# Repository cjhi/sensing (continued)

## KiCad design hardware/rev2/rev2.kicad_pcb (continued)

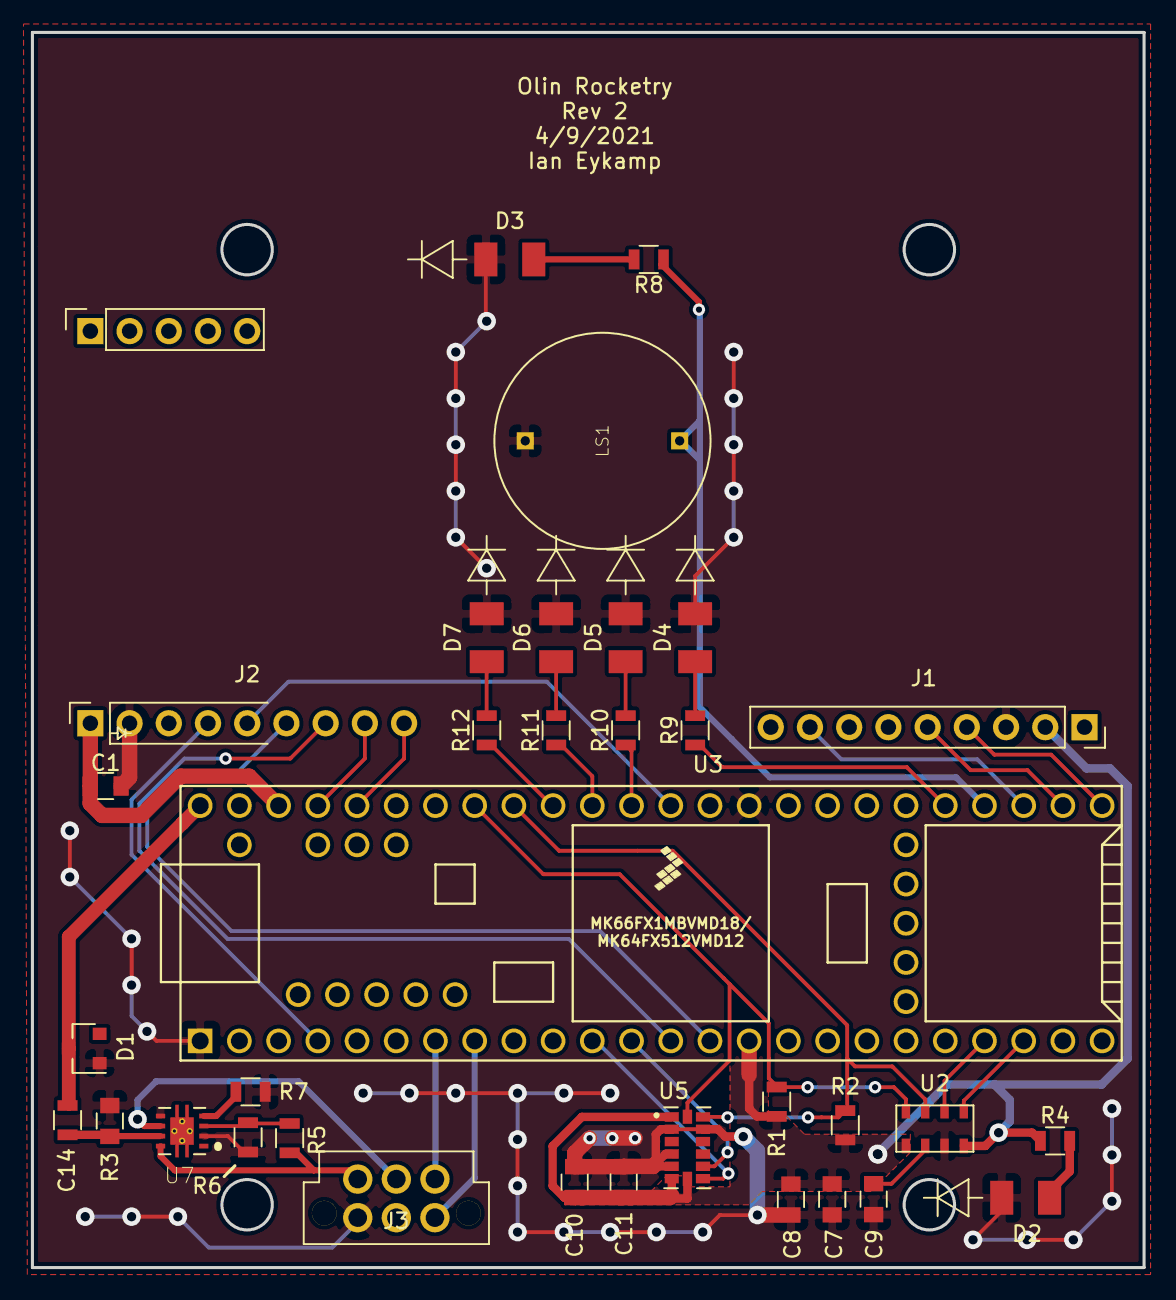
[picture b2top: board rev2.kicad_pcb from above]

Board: 2 copper layers, 72.0 x 80.0 mm, 34 parts (1 on the bottom side), 38 nets.

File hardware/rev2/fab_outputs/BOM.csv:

"Comment","Designator","Footprint","LCSC Part #","LCSC Part Type"

"Conn_02x03_Odd_Even","J3","Molex_Nano-Fit_105312-1106","",""

"LED","D2,D3,D4,D5,D6,D7","AA3528LSECKT-J4","",""

"PKB24SPCH3601-B0","LS1","PT-1340","",""

"100n","C7,C9,C10","C_0805_OEM","",""

"10u","C8","C_0805_OEM","",""

"R_4.99K","R1,R2","R_0805_OEM","",""

"MPL3115A2","U2","MPL3115A2","",""

"Teensy3.6","U3","Teensy3-6","",""

"1u","C11","C_0805_OEM","",""

"ADXL345BCCZ","U5","ADXL345","",""

"RFM9X_header","J2","RFM9X_header","",""

"Conn_01x09_Female","J1","PinSocket_1x09_P2.54mm_Vertical","",""

"R_20k","R5","R_0805_OEM","",""

"C_1uF","C14","C_0805_OEM","",""

"R_8k","R6","R_0805_OEM","",""

"R_475","R7","R_0805_OEM","",""

"TPS2113ADRBR","U7","TPS2113ADRBR","",""

"C_10uF","C1","C_0805_OEM","",""

"D_Zener","D1","SOT-23","",""

"R_20","R3","R_0805_OEM","",""

"R_750","R4,R8,R9,R10,R11,R12","R_0805_OEM","",""

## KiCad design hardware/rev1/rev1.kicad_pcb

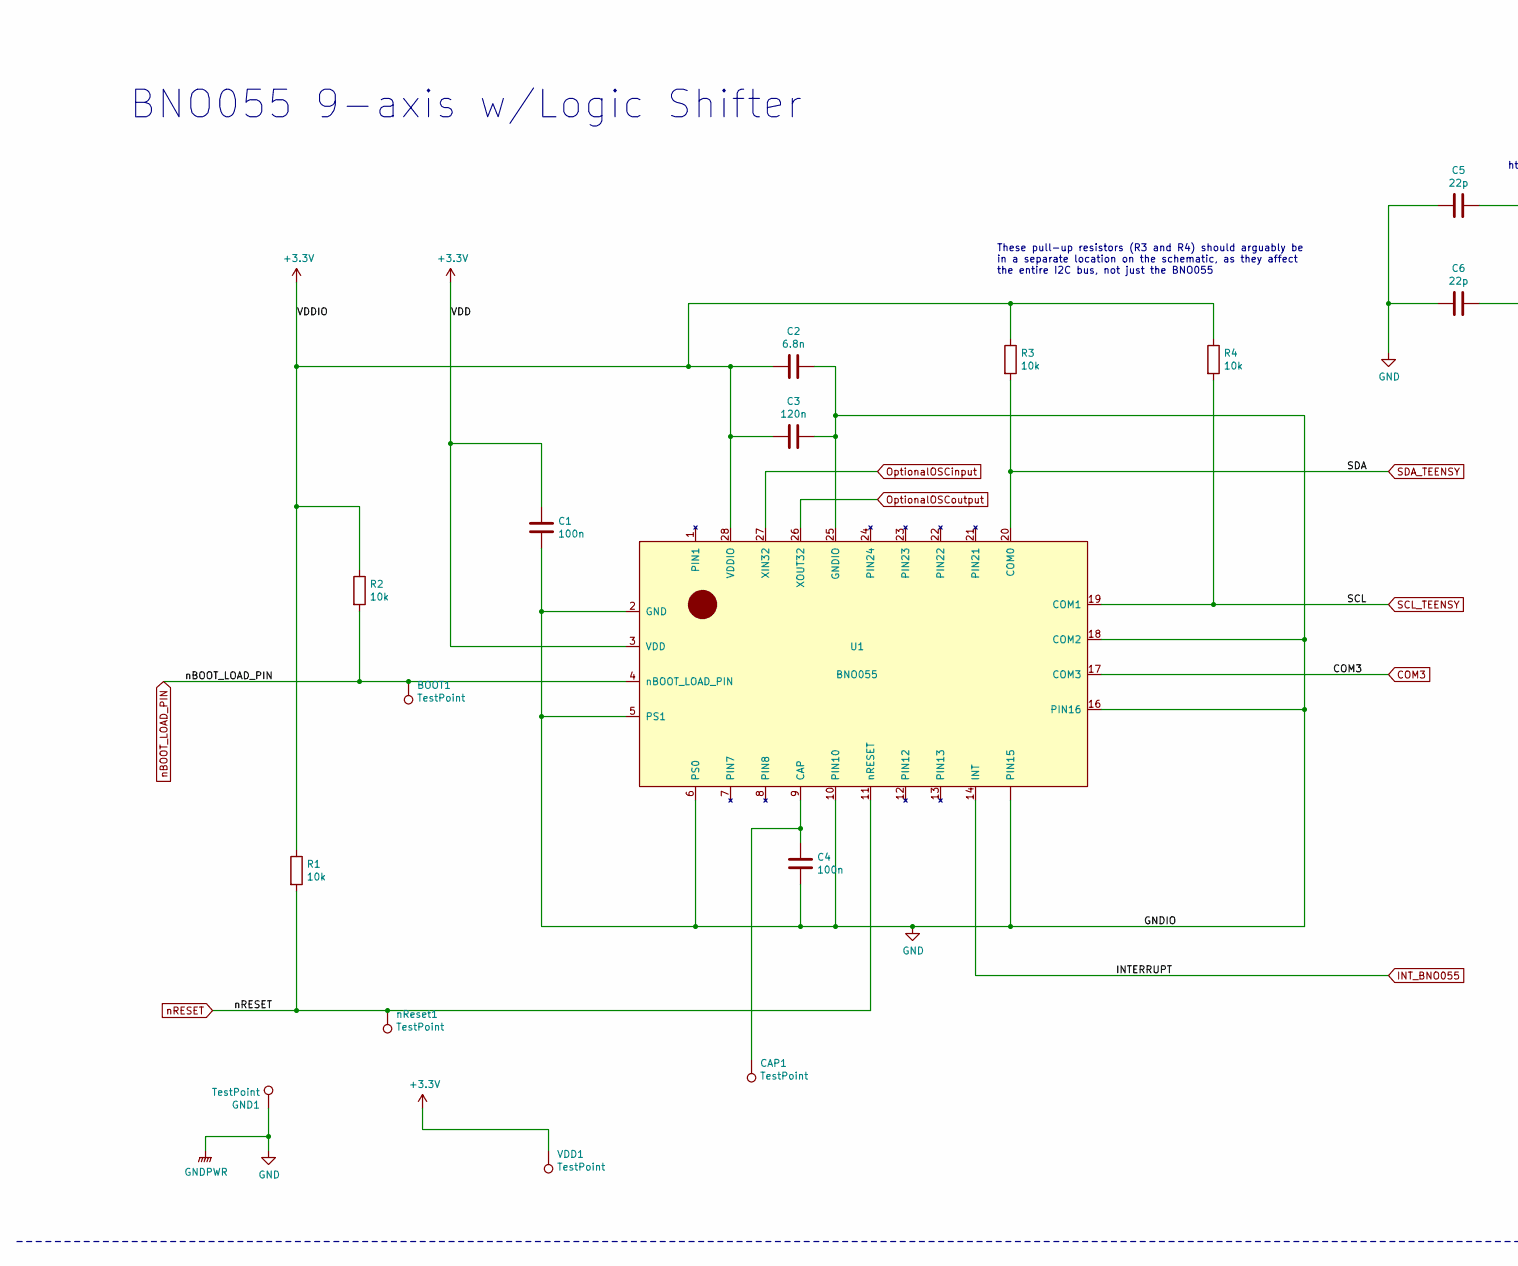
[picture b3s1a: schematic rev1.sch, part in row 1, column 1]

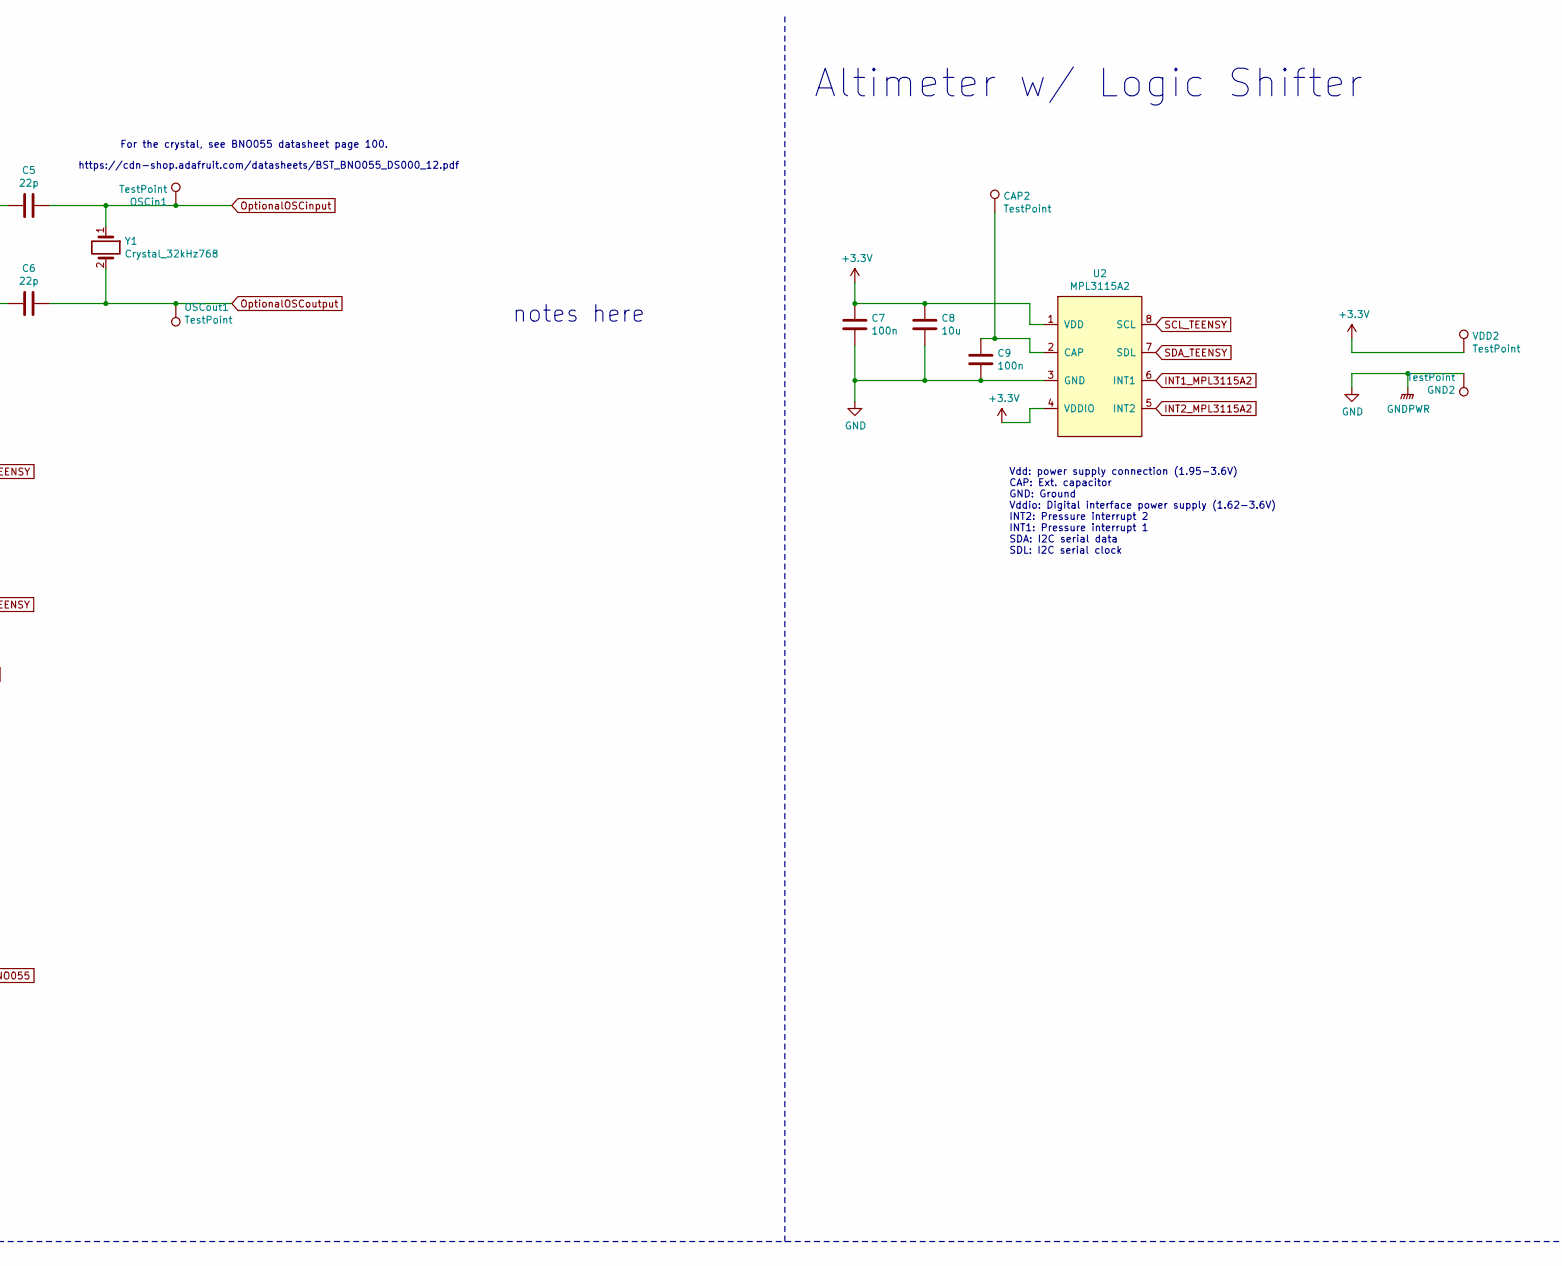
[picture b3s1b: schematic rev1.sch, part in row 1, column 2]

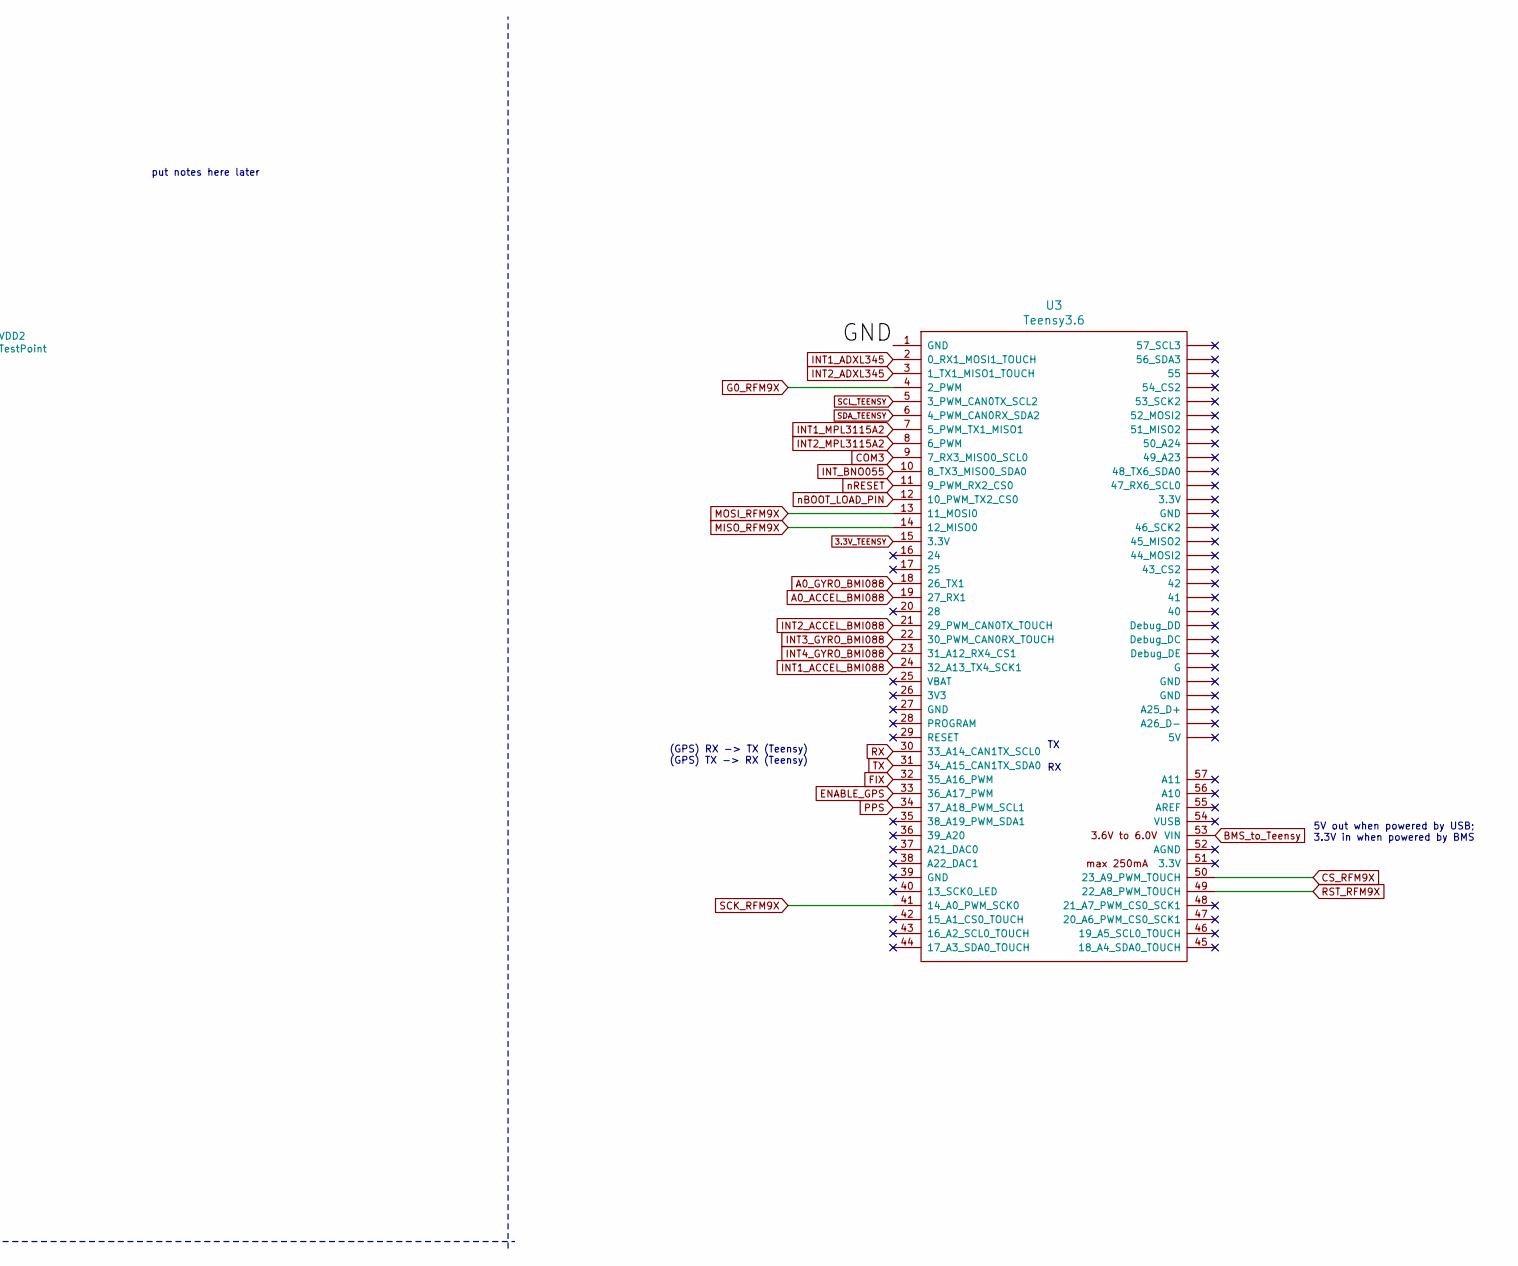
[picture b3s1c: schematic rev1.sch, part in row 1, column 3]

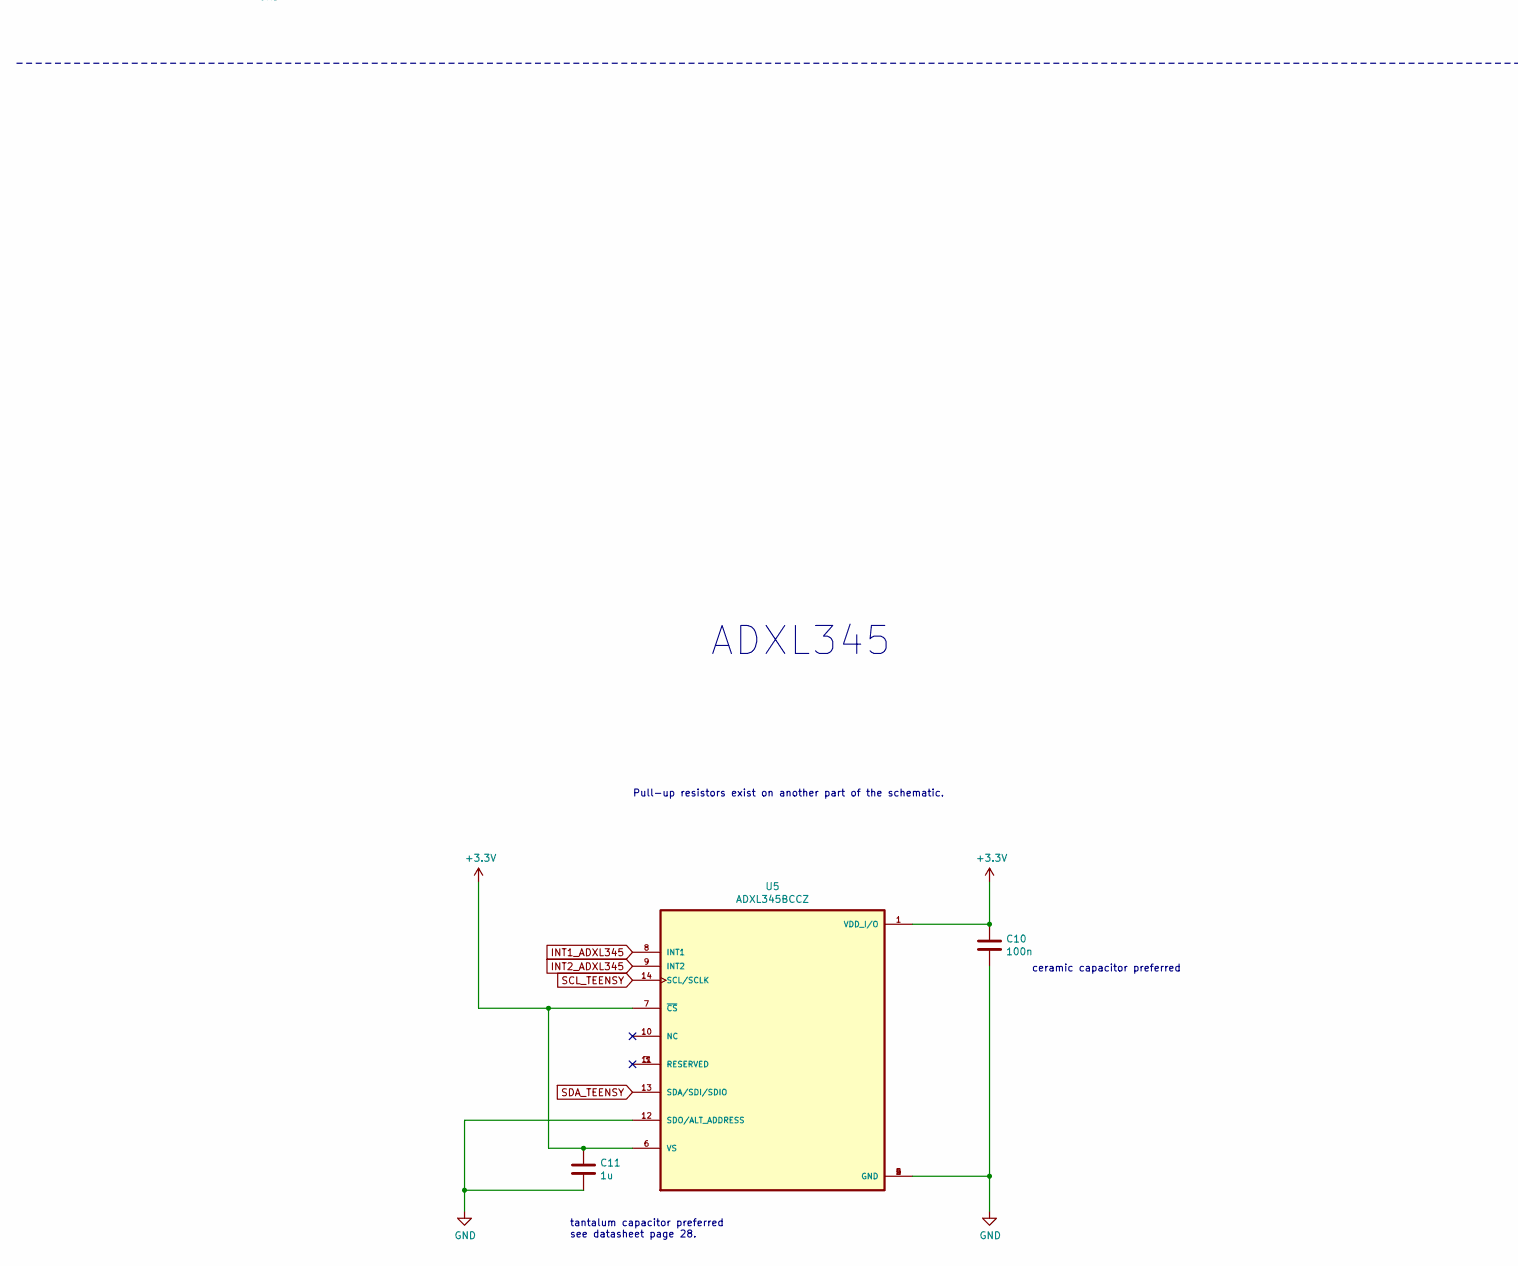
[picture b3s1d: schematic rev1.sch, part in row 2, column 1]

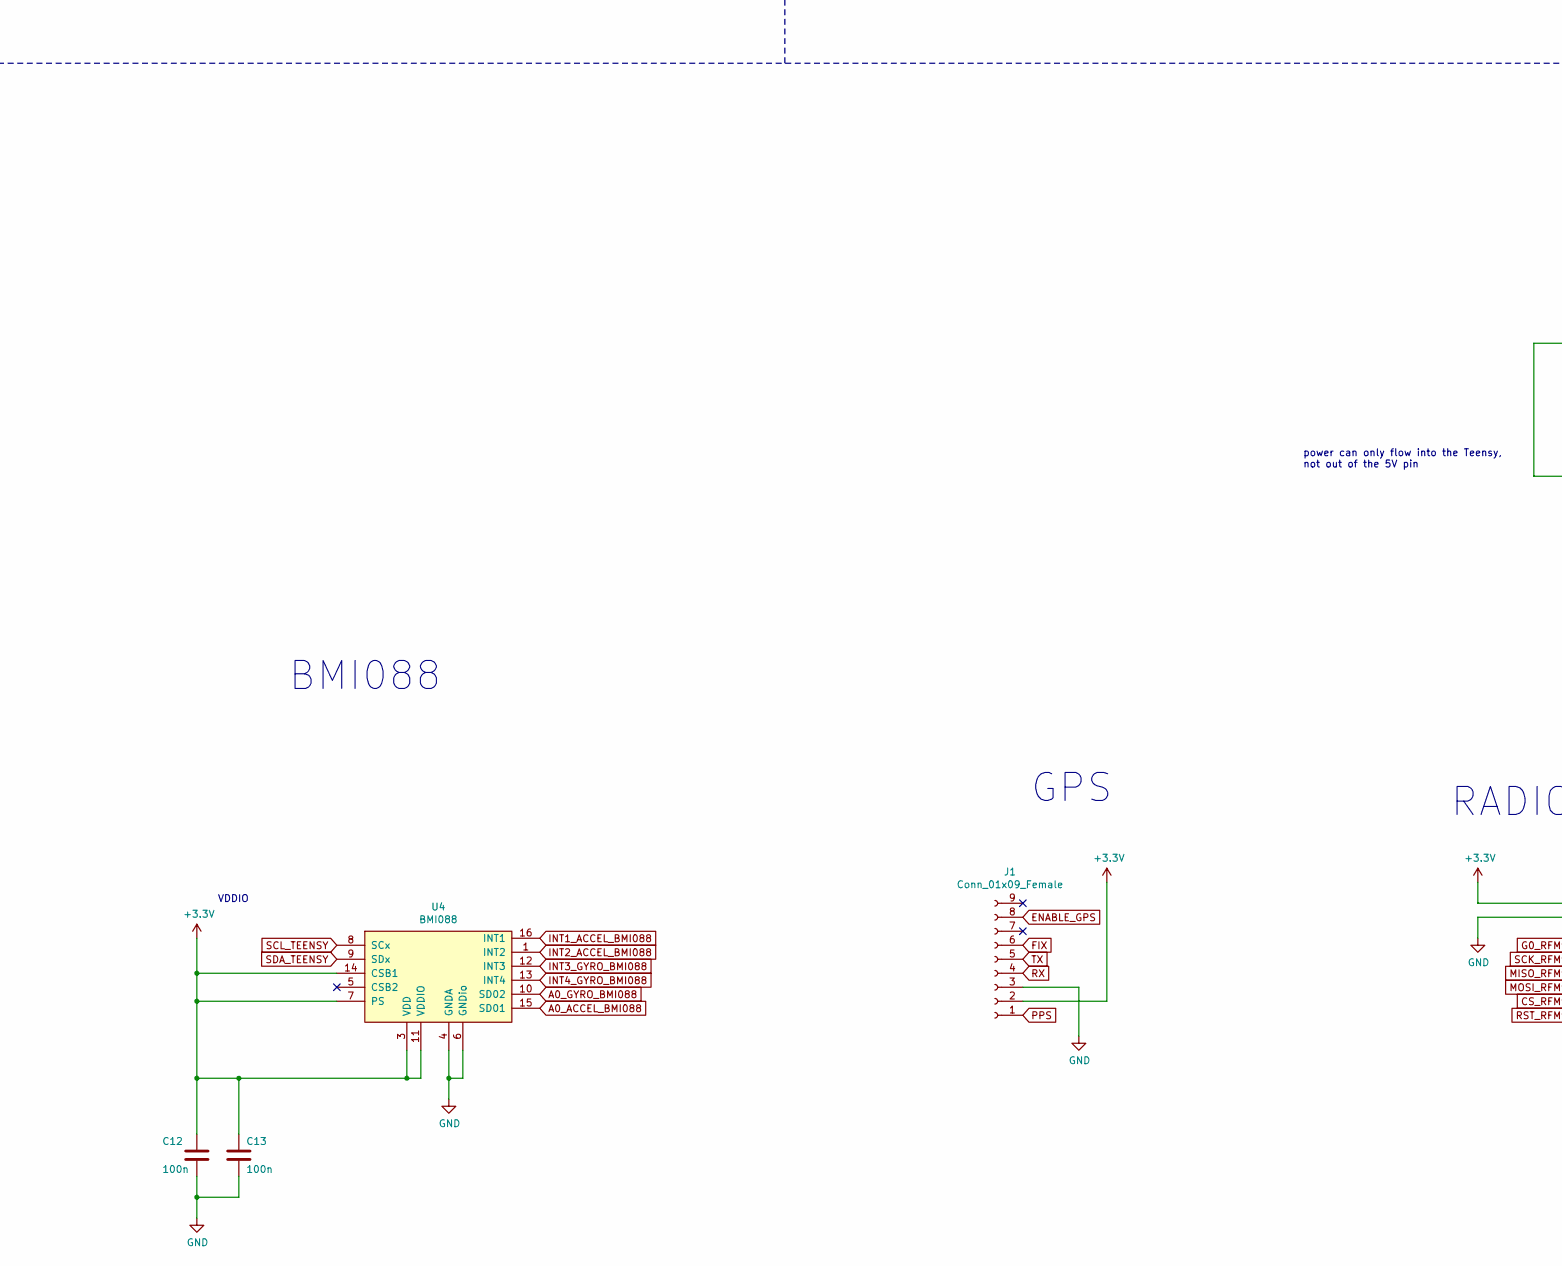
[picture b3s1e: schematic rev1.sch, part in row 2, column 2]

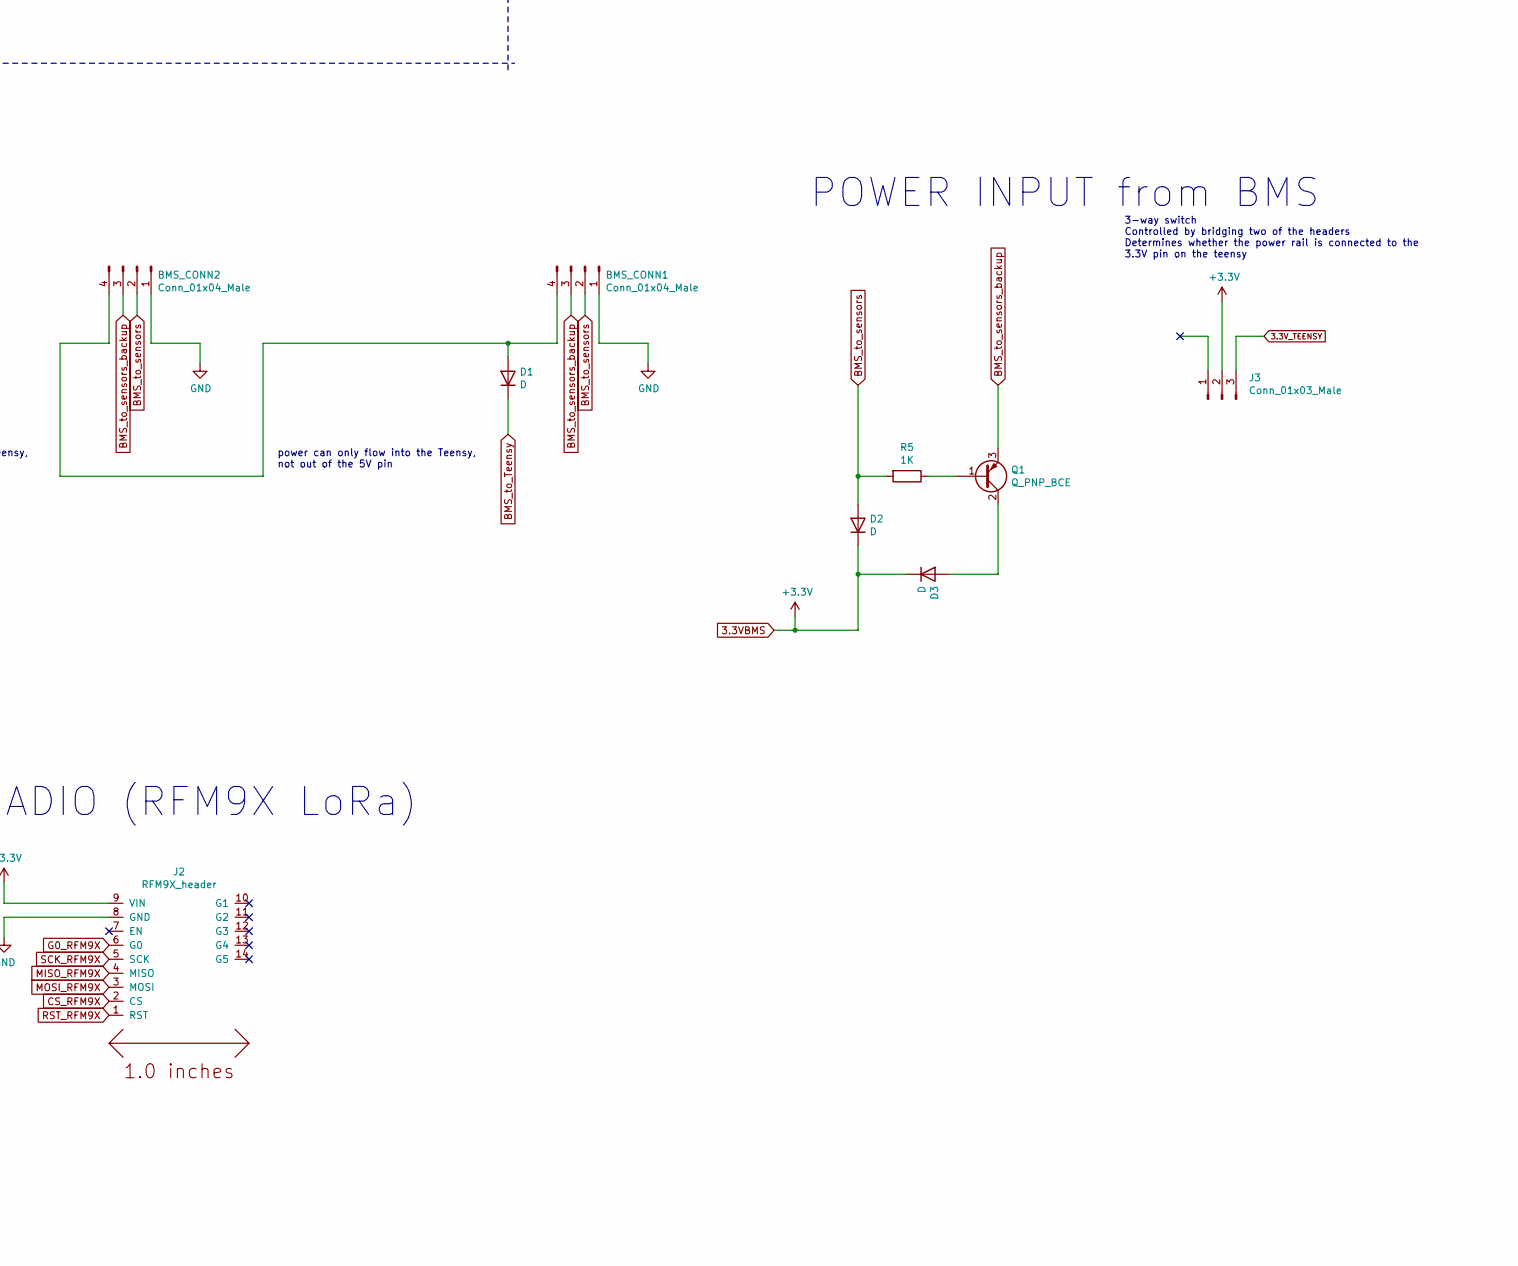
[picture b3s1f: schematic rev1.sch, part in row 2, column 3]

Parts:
BMS_CONN1, BMS_CONN2: Conn_01x04_Male; PinHeader_1x04_P2.54mm_Vertical
BOOT1: TestPoint; Test-Point-Pin_Drill2.79mm
C1, C4, C7, C9: 100n; C_0805_OEM
C2: 6.8n; C_0805_OEM
C3: 120n; C_0805_OEM
C5, C6: 22p; C_0805_OEM
C8: 10u; C_0805_OEM
C10: 100n; C_0805_OEM; MPN 478-3352-1-ND
C11: 1u; C_0805_OEM; MPN 1276-2887-1-ND
C12, C13: 100n; C_0805_OEM; MPN 1276-6717-1-ND
CAP1, CAP2: TestPoint; Test-Point-Pin_Drill2.79mm
D1, D2, D3: D; D_0805_OEM
GND1, GND2: TestPoint; Test-Point-Pin_Drill2.79mm
J1: Conn_01x09_Female; PinSocket_1x09_P2.54mm_Vertical
J2: RFM9X_header
J3: Conn_01x03_Male; PinHeader_1x03_P2.54mm_Vertical
OSCin1: TestPoint; Test-Point-Pin_Drill2.79mm
OSCout1: TestPoint; Test-Point-Pin_Drill2.79mm
Q1: Q_PNP_BCE; TO-220-3_Horizontal_TabDown
R1, R2, R3, R4: 10k; R_0805_OEM
R5: 1K; R_0805_OEM; MPN P1.07KDACT-ND
U1: BNO055
U2: MPL3115A2
U3: Teensy3.6; Teensy3-6
U4: BMI088; bmi088
U5: ADXL345BCCZ; ADXL345
VDD1, VDD2: TestPoint; Test-Point-Pin_Drill2.79mm
Y1: Crystal_32kHz768; FC-135_3.2x1.5mm; MPN SER4084CT-ND
nReset1: TestPoint; Test-Point-Pin_Drill2.79mm

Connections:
3.3VBMS: C1.1, C2.2, C3.2, C7.1, C8.1, C10.1, C11.1, C12.1, C13.1, D2.1 (K), D3.1 (K), J1.2, J2.9 (VIN), J3.2, R1.1, R2.1, R3.1, R4.1, U1.3 (VDD), U1.28 (VDDIO), U2.1 (VDD), U2.4 (VDDIO), U4.3 (VDD), U4.7 (PS), U4.11 (VDDIO), U4.14 (CSB1), U5.1 (VDD_I/O), U5.6 (VS), U5.7 (~CS), VDD1.1, VDD2.1
3.3V_TEENSY: J3.3, U3.15 (3.3V)
A0_ACCEL_BMI088: U3.19 (27_RX1), U4.15 (SD01)
A0_GYRO_BMI088: U3.18 (26_TX1), U4.10 (SD02)
BMS_to_Teensy: D1.1 (K), U3.53 (VIN)
BMS_to_sensors: BMS_CONN1.2, BMS_CONN2.2, D2.2 (A), R5.2
BMS_to_sensors_backup: BMS_CONN1.3, BMS_CONN2.3, Q1.3 (E)
COM3: U1.17 (COM3), U3.9 (7_RX3_MISO0_SCL0)
CS_RFM9X: J2.2 (CS), U3.50 (23_A9_PWM_TOUCH)
ENABLE_GPS: J1.8, U3.33 (36_A17_PWM)
FIX: J1.6, U3.32 (35_A16_PWM)
G0_RFM9X: J2.6 (G0), U3.4 (2_PWM)
GND: BMS_CONN1.1, BMS_CONN2.1, C1.2, C2.1, C3.1, C4.2, C5.2, C6.2, C7.2, C8.2, C9.2, C10.2, C11.2, C12.2, C13.2, GND1.1, GND2.1, J1.3, J2.8 (GND), U1.2 (GND), U1.5 (PS1), U1.6 (PS0), U1.10 (PIN10), U1.16 (PIN16), U1.18 (COM2), U1.25 (GNDIO), U1.~ (PIN15), U2.3 (GND), U3.1 (GND), U4.4 (GNDA), U4.6 (GNDio), U5.2 (GND), U5.4 (GND), U5.5 (GND), U5.12 (SDO/ALT_ADDRESS)
INT1_ACCEL_BMI088: U3.24 (32_A13_TX4_SCK1), U4.16 (INT1)
INT1_ADXL345: U3.2 (0_RX1_MOSI1_TOUCH), U5.8 (INT1)
INT1_MPL3115A2: U2.6 (INT1), U3.7 (5_PWM_TX1_MISO1)
INT2_ACCEL_BMI088: U3.21 (29_PWM_CAN0TX_TOUCH), U4.1 (INT2)
INT2_ADXL345: U3.3 (1_TX1_MISO1_TOUCH), U5.9 (INT2)
INT2_MPL3115A2: U2.5 (INT2), U3.8 (6_PWM)
INT3_GYRO_BMI088: U3.22 (30_PWM_CAN0RX_TOUCH), U4.12 (INT3)
INT4_GYRO_BMI088: U3.23 (31_A12_RX4_CS1), U4.13 (INT4)
INT_BNO055: U1.14 (INT), U3.10 (8_TX3_MISO0_SDA0)
MISO_RFM9X: J2.4 (MISO), U3.14 (12_MISO0)
MOSI_RFM9X: J2.3 (MOSI), U3.13 (11_MOSI0)
unnamed: BMS_CONN1.4, BMS_CONN2.4, D1.2 (A)
unnamed: C4.1, CAP1.1, U1.9 (CAP)
unnamed: C9.1, CAP2.1, U2.2 (CAP)
unnamed: D3.2 (A), Q1.2 (C)
unnamed: Q1.1 (B), R5.1
unnamed: U5.3 (RESERVED), U5.11 (RESERVED)
OptionalOSCinput: C5.1, OSCin1.1, U1.27 (XIN32), Y1.1
OptionalOSCoutput: C6.1, OSCout1.1, U1.26 (XOUT32), Y1.2
PPS: J1.1, U3.34 (37_A18_PWM_SCL1)
RST_RFM9X: J2.1 (RST), U3.49 (22_A8_PWM_TOUCH)
RX: J1.4, U3.30 (33_A14_CAN1TX_SCL0)
SCK_RFM9X: J2.5 (SCK), U3.41 (14_A0_PWM_SCK0)
SCL_TEENSY: R4.2, U1.19 (COM1), U2.8 (SCL), U3.5 (3_PWM_CAN0TX_SCL2), U4.8 (SCx), U5.14 (SCL/SCLK)
SDA_TEENSY: R3.2, U1.20 (COM0), U2.7 (SDL), U3.6 (4_PWM_CAN0RX_SDA2), U4.9 (SDx), U5.13 (SDA/SDI/SDIO)
TX: J1.5, U3.31 (34_A15_CAN1TX_SDA0)
nBOOT_LOAD_PIN: BOOT1.1, R2.2, U1.4 (nBOOT_LOAD_PIN), U3.12 (10_PWM_TX2_CS0)
nRESET: R1.2, U1.11 (nRESET), U3.11 (9_PWM_RX2_CS0), nReset1.1

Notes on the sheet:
Altimeter w/ Logic Shifter
put notes here later
BNO055 9-axis w/Logic Shifter
notes here
Vdd: power supply connection (1.95-3.6V) CAP: Ext. capacitor GND: Ground Vddio: Digital interface power supply (1.62-3.6V) INT2: Pressure interrupt 2 INT1: Pressure interrupt 1 SDA: I2C serial data SDL: I2C serial clock
For the crystal, see BNO055 datasheet page 100.
https://cdn-shop.adafruit.com/datasheets/BST_BNO055_DS000_12.pdf
VDDIO
Pull-up resistors exist on another part of the schematic.
ADXL345
BMI088
RADIO (RFM9X LoRa)
These pull-up resistors (R3 and R4) should arguably be in a separate location on the schematic, as they affect the entire I2C bus, not just the BNO055
POWER INPUT from BMS
GPS
ceramic capacitor preferred
tantalum capacitor preferred see datasheet page 28.
3-way switch Controlled by bridging two of the headers Determines whether the power rail is connected to the 3.3V pin on the teensy
TX RX
(GPS) RX -> TX (Teensy) (GPS) TX -> RX (Teensy)
5V out when powered by USB; 3.3V in when powered by BMS
power can only flow into the Teensy, not out of the 5V pin

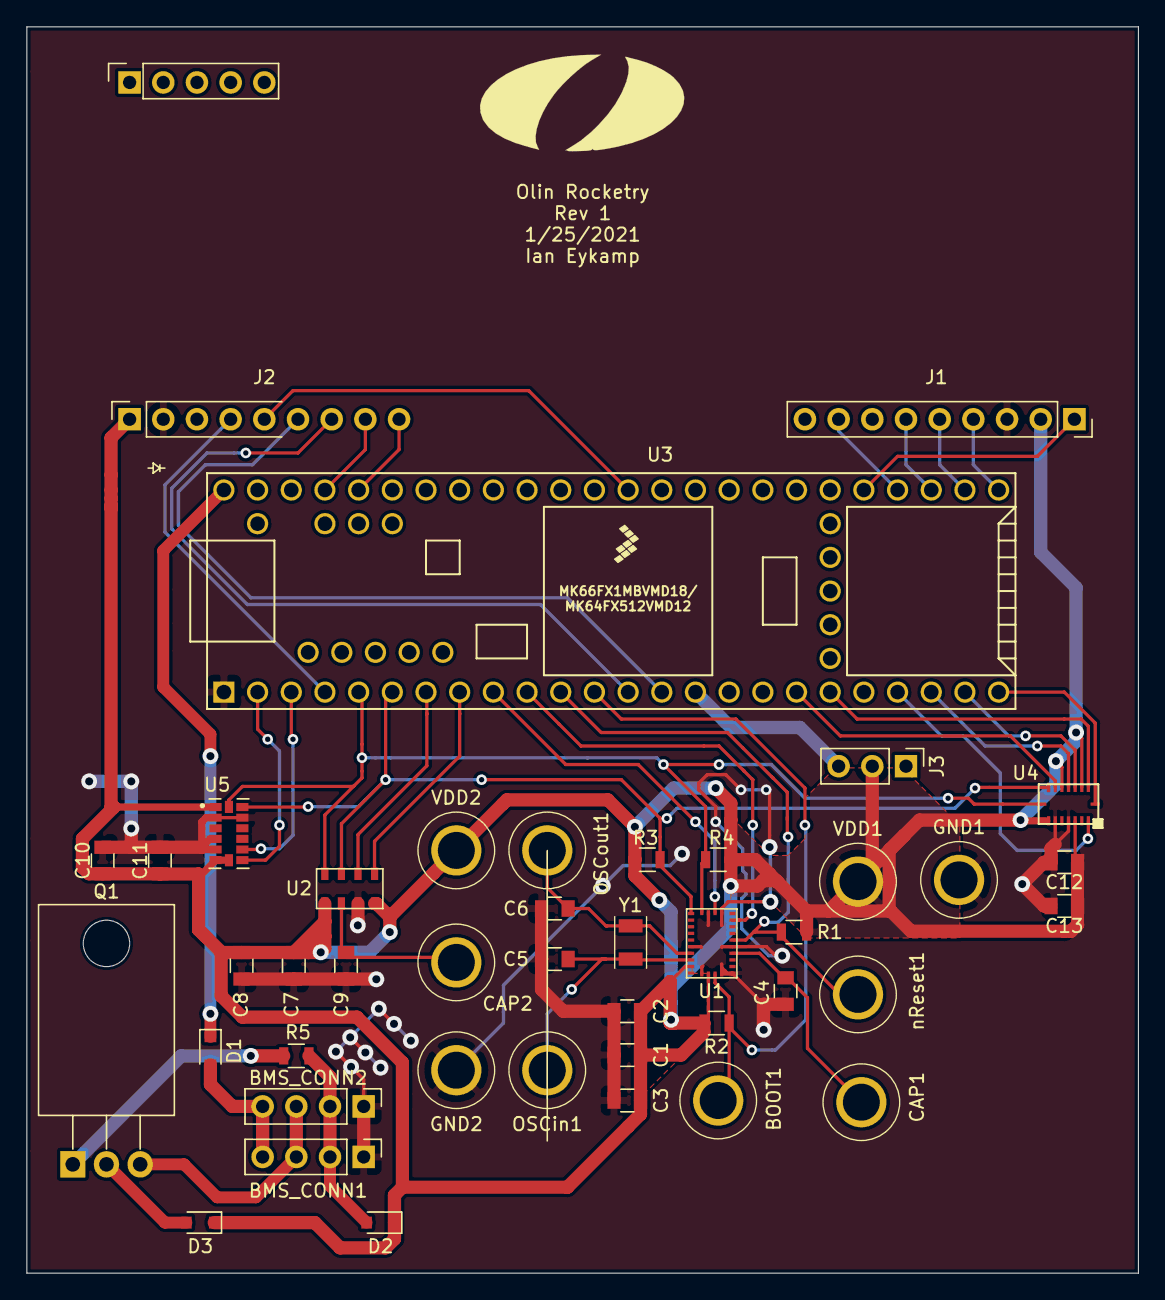
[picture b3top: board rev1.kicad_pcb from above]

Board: 2 copper layers, 83.8 x 94.0 mm, 43 parts (1 on the bottom side), 41 nets.

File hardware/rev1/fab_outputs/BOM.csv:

"Comment";"Designator";"Footprint";"LCSC Part #";"LCSC Part Type"
"100n";"C1,C4,C7,C9,C10,C12,C13";"C_0805_OEM";"";""
"6.8n";"C2";"C_0805_OEM";"";""
"120n";"C3";"C_0805_OEM";"";""
"22p";"C5,C6";"C_0805_OEM";"";""
"10u";"C8";"C_0805_OEM";"";""
"10k";"R1,R2,R3,R4";"R_0805_OEM";"";""
"MPL3115A2";"U2";"MPL3115A2";"";""
"Teensy3.6";"U3";"Teensy3-6";"";""
"Crystal_32kHz768";"Y1";"FC-135_3.2x1.5mm";"";""
"BNO055";"U1";"BNO055";"";""
"TestPoint";"BOOT1,CAP1,CAP2,GND1,GND2,nReset1,OSCin1,OSCout1,VDD1,VDD2";"Test-Point-Pin_Drill2.79mm";"";""
"1u";"C11";"C_0805_OEM";"";""
"BMI088";"U4";"bmi088";"";""
"ADXL345BCCZ";"U5";"ADXL345";"";""
"RFM9X_header";"J2";"RFM9X_header";"";""
"Conn_01x09_Female";"J1";"PinSocket_1x09_P2.54mm_Vertical";"";""
"D";"D1,D2,D3";"D_0805_OEM";"";""
"Conn_01x03_Male";"J3";"PinHeader_1x03_P2.54mm_Vertical";"";""
"Conn_01x04_Male";"BMS_CONN1,BMS_CONN2";"PinHeader_1x04_P2.54mm_Vertical";"";""
"Q_PNP_BCE";"Q1";"TO-220-3_Horizontal_TabDown";"";""
"1K";"R5";"R_0805_OEM";"";""
"";"G***";"OLIN_O";"";""

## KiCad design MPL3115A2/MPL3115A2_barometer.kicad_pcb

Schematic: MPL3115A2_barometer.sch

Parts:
C1, C3: 100n; C_0805_OEM
C2: 10u; C_0805_OEM
U1: MPL3115A2

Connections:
GND: C1.2, C2.2, C3.2, U1.3
INT1: U1.6
INT2: U1.5
unnamed: C3.1, U1.2
SCL: U1.8
SDL: U1.7
VDDIO: C1.1, C2.1, U1.1, U1.4

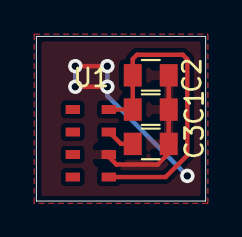
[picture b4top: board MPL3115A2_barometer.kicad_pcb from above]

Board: 2 copper layers, 9.4 x 9.1 mm, 4 parts (0 on the bottom side), 3 nets.

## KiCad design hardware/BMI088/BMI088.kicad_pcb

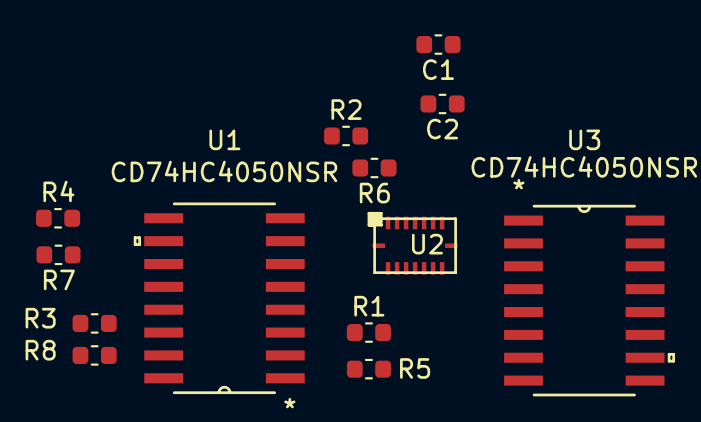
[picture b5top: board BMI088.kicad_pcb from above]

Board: 2 copper layers, 13 parts (0 on the bottom side), 16 nets, no tracks yet.

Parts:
C1, C2: C_100nF; C_0603_1608Metric
R1, R2, R3, R4, R5, R6, R7, R8: R_0; R_0603_1608Metric
U1, U3: CD74HC4050NSR
U2: BMI088; bmi088

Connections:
+3V3: C1.1, C2.1, U1.1, U2.3, U2.7, U2.11, U2.14, U3.1
/INT1_ACCEL: R5.1, U1.2, U2.16
/INT1_ACCEL_5: R1.2, R5.2
/INT2_ACCEL: R6.1, U1.6, U2.1
/INT2_ACCEL_5: R2.2, R6.2
/INT3_GYRO: R7.1, U1.10, U2.12
/INT3_GYRO_5: R4.1, R7.2
/INT4_GYRO: R8.1, U1.15, U2.13
/INT4_GYRO_5: R3.1, R8.2
/SCL: U2.8, U3.2
/SDA: U2.9, U3.4
GND: C1.2, C2.2, U1.8, U2.4, U2.6, U3.8
unnamed: R1.1, U1.3
unnamed: R2.1, U1.7
unnamed: R3.2, U1.14
unnamed: R4.2, U1.9

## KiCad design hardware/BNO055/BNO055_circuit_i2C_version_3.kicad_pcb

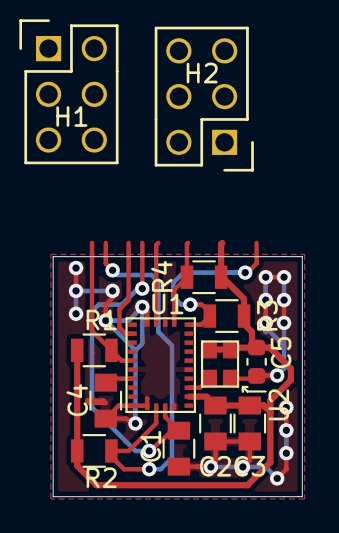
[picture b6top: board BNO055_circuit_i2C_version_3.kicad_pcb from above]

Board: 2 copper layers, 13.8 x 13.3 mm, 13 parts (0 on the bottom side), 11 nets.

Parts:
C1, C4: 100nF; C_0805_OEM
C2: 6.8nF; C_0805_OEM
C3: 120nF; C_0805_OEM
C5: 0.01u; C_0603_1608Metric
H1, H2: Header_2x3; Pin_Header_Straight_2x03
R1: Optional 10k; R_0805_OEM
R2: Pull-up 10k; R_0805_OEM
R3, R4: Rpull; R_0805_OEM
U1: BNO055
U2: ASDMB-xxxMHz; ASDK2-32.768KHZ-LR-T3

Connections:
COM3: H2.1, U1.17
GND: C1.2, C2.1, C3.1, C4.2, C5.1, H1.1, U1.2, U1.5, U1.6, U1.10, U1.16, U1.18, U1.25, U2.2
INT: H2.6, U1.14
unnamed: C4.1, U1.9
OptionalOSCinput: U1.27, U2.3
SCL: H2.3, R4.2, U1.19
SDA: H2.5, R3.2, U1.20
VDD: C1.1, H1.3, U1.3
VDDIO: C2.2, C3.2, C5.2, H1.5, R1.1, R2.1, R3.1, R4.1, U1.28, U2.1, U2.4
nBOOT_LOAD_PIN: H2.2, R2.2, U1.4
nRESET: H2.4, R1.2, U1.11

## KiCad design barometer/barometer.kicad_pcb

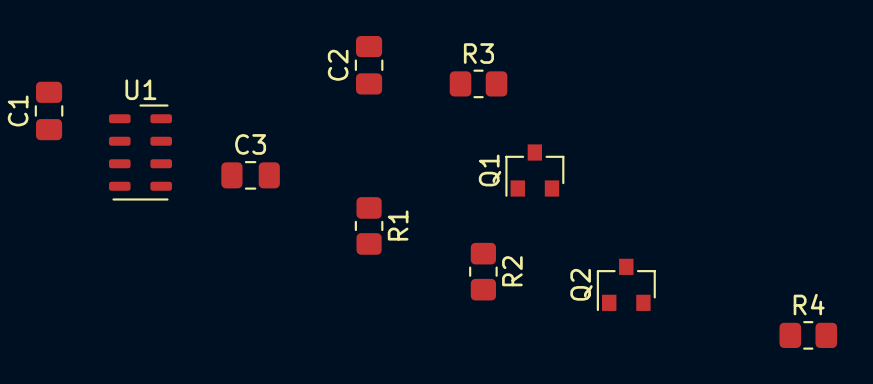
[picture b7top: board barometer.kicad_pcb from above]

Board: 2 copper layers, 10 parts (0 on the bottom side), 7 nets, no tracks yet.

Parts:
C1, C3: 100nF; C_0805_2012Metric_Pad1.18x1.45mm_HandSolder
C2: 10uF; C_0805_2012Metric_Pad1.18x1.45mm_HandSolder
Q1, Q2: BSS138; SOT-23
R1, R2, R3, R4: R_10K; R_0805_2012Metric_Pad1.20x1.40mm_HandSolder
U1: MPL3115A2; NXP_LGA-8_3x5mm_P1.25mm_H1.1mm

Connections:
+3V3: Q1.1, Q2.1, R1.1, R2.1
/SCL_3V: Q2.2, R2.2
/SCL_RAW: Q2.3, R4.2
/SDA_3V: Q1.2, R1.2
/SDA_RAW: Q1.3, R3.2
GND: C1.2, C2.1, C2.2, C3.1, C3.2, R3.1, R4.1, U1.1, U1.3
unnamed: C1.1, U1.2
